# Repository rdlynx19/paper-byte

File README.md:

# Paper Byte

Paper Byte is ESP32-S3 based e-reader,
This repository contains the PCB design files, the CAD files for the case, and the firmware to read and parse EPUB files. 

For a more detailed guide, visit my blog post - [PaperByte](https://pushkardave.com/paper-byte)

## Overview

Paper Byte parses EPUB files straight off an SD card and renders them on an e-ink screen, with three-button navigation (prev / next / select) driving a small state machine: Library, Reader, Menu, Settings, Table of Contents, and a Wi-Fi file transfer mode.

- Unzips and parses EPUBs (XHTML + metadata) from an SD card
- Reflowable text layout: word-wrap, adjustable font size, margins
- Cover art extraction and a library grid with cached thumbnails
- Table of contents / chapter jump
- Persistent reading position per book, survives power loss
- Battery percentage from a MAX17048 fuel gauge
- Sleeps to the book's cover at zero power and wakes straight back into the reader
- Wireless library management: the device hosts its own Wi-Fi access point and a small HTTP page to upload/delete EPUBs

## Hardware

| Component | Role |
|---|---|
| Adafruit ESP32-S3 Feather | Parses EPUBs, drives the display, runs the whole app |
| Waveshare 5" E-Paper Display + driver HAT | Renders pages over SPI |
| Adafruit SD Card module | EPUB storage, hot-swappable (card-detect pin) |
| MAX17048 fuel gauge (on the Feather) | Battery % over I2C |
| 3 tactile switches | Prev / Next / Select |
| 1S LiPo battery | Power, charged over the Feather's USB-C |

A custom through-hole PCB (`pcb/`) ties the Feather, SD module, and e-paper HAT together on SPI buses. The 3D-printed enclosure is in `cad/`.

## Software Architecture

```
EPUB (zip) -> unzip/parse chapter -> word-wrap into pages sized to the display -> render to e-paper
```

- Each chapter is parsed and laid out once, then cached in RAM — flipping pages just re-renders from the cache; only crossing into a new chapter costs a re-parse.
- Reading position, settings, and cover art are all cached to the SD card.

### Code layout (`code/src/`)

- `epub/` — ZIP extraction (`miniz`), XHTML parsing (`tinyxml2` + a small "rubbish" HTML parser), EPUB metadata
- `model/` — page/block layout model that turns parsed HTML into fixed-size pages
- `display/` — e-paper driver (`EPD_5in0`), drawing primitives (`GUI_Paint`), bitmap fonts, cover art rendering
- `storage/` — SD-backed reading position and settings persistence
- `power/` — MAX17048 battery fuel gauge wrapper
- `network/` — `FileServer`, the AP-mode Wi-Fi file manager

## Wireless File Manager

From the Library menu, entering File Transfer mode starts a Wi-Fi access point (SSID/password in `code/src/config.h`) and a small web page for uploading/deleting EPUBs. Idle-timeout sleep is suspended while the mode is active; exiting tears down Wi-Fi and re-scans the library.

## Future Work

- Partial e-ink refresh for page turns (currently a full refresh every page)
- Bookmarks
- A dedicated low-battery/charging screen

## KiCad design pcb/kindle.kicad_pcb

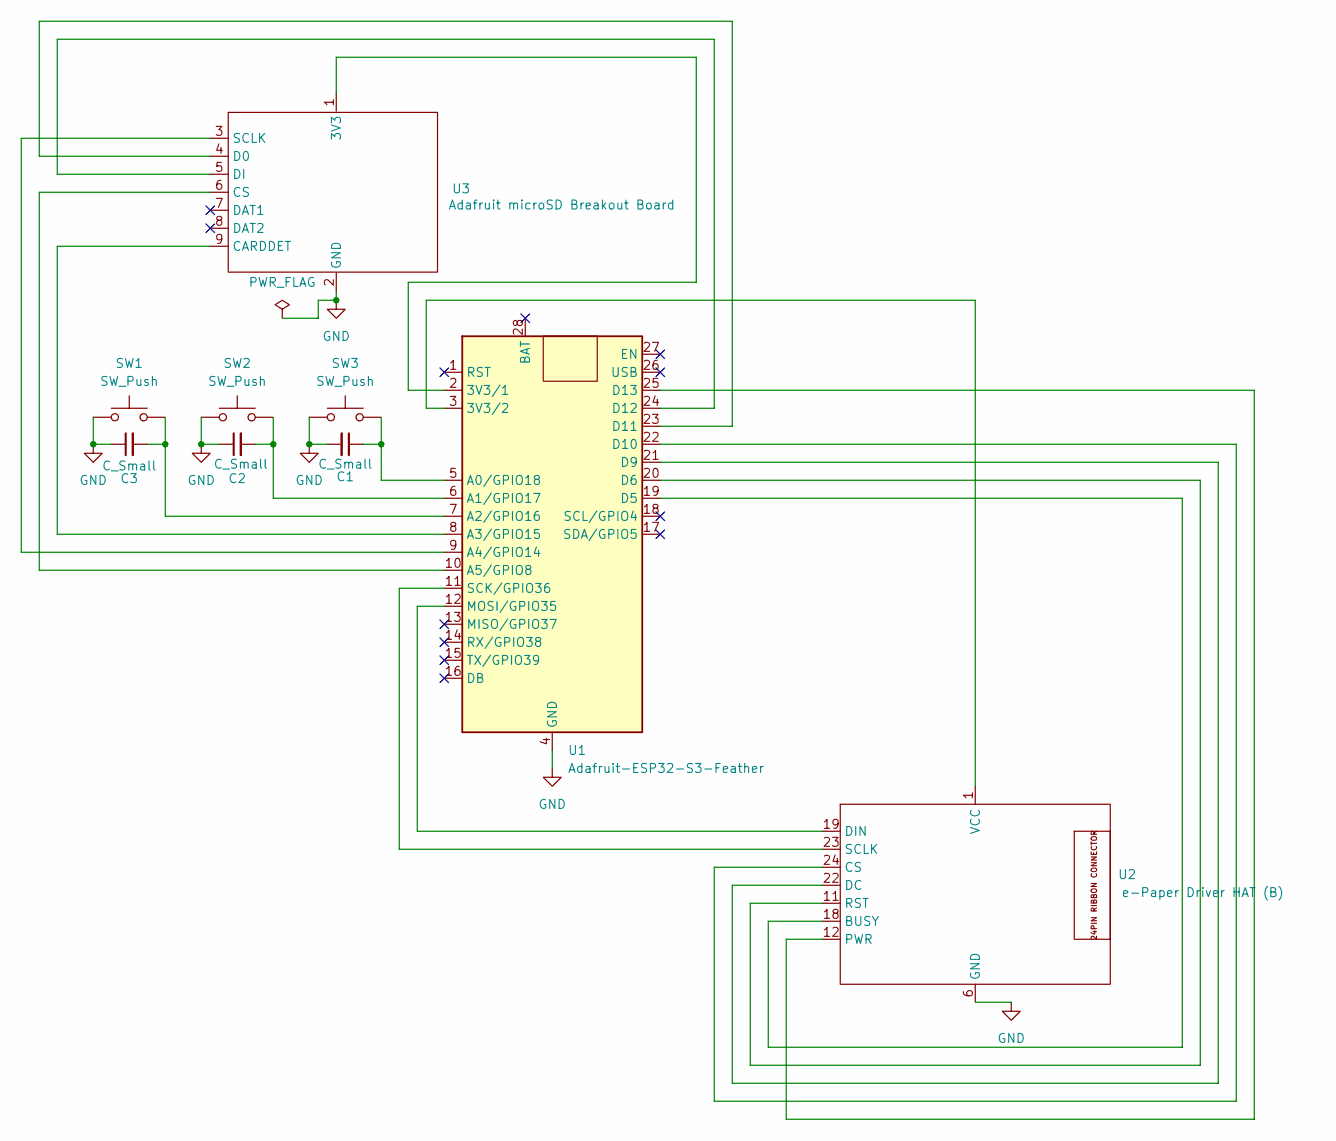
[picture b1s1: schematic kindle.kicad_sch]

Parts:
C1, C2, C3: C_Small; C_Disc_D3.0mm_W1.6mm_P2.50mm
SW1, SW2, SW3: SW_Push; SW_PUSH_6mm_H5mm
U1: Adafruit-ESP32-S3-Feather; Adafruit_ESP32_S3_Feather_WithMountingHoles
U2: e-Paper Driver HAT (B); MODULE_RASPBERRY_PI_ZERO_2_W
U3: Adafruit microSD Breakout Board; MODULE_MICROSD_SPI_OR_SDIO_CARD

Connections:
GND: C1.2, C2.1, C3.1, SW1.1, SW2.1, SW3.1, U1.4 (GND), U2.6 (GND), U3.2 (GND)
unnamed: U1.2 (3V3/1), U3.1 (3V3)
unnamed: U1.3 (3V3/2), U2.1 (VCC)
unnamed: C1.1, SW3.2, U1.5 (A0/GPIO18)
unnamed: C2.2, SW2.2, U1.6 (A1/GPIO17)
unnamed: C3.2, SW1.2, U1.7 (A2/GPIO16)
unnamed: U1.8 (A3/GPIO15), U3.9 (CARDDET)
unnamed: U1.9 (A4/GPIO14), U3.3 (SCLK)
unnamed: U1.10 (A5/GPIO8), U3.6 (CS)
unnamed: U1.19 (D5), U2.18 (BUSY)
unnamed: U1.20 (D6), U2.11 (RST)
unnamed: U1.21 (D9), U2.22 (DC)
unnamed: U1.22 (D10), U2.24 (CS)
unnamed: U1.23 (D11), U3.4 (D0)
unnamed: U1.24 (D12), U3.5 (DI)
unnamed: U1.25 (D13), U2.12 (PWR)
unnamed: U1.12 (MOSI/GPIO35), U2.19 (DIN)
unnamed: U1.11 (SCK/GPIO36), U2.23 (SCLK)

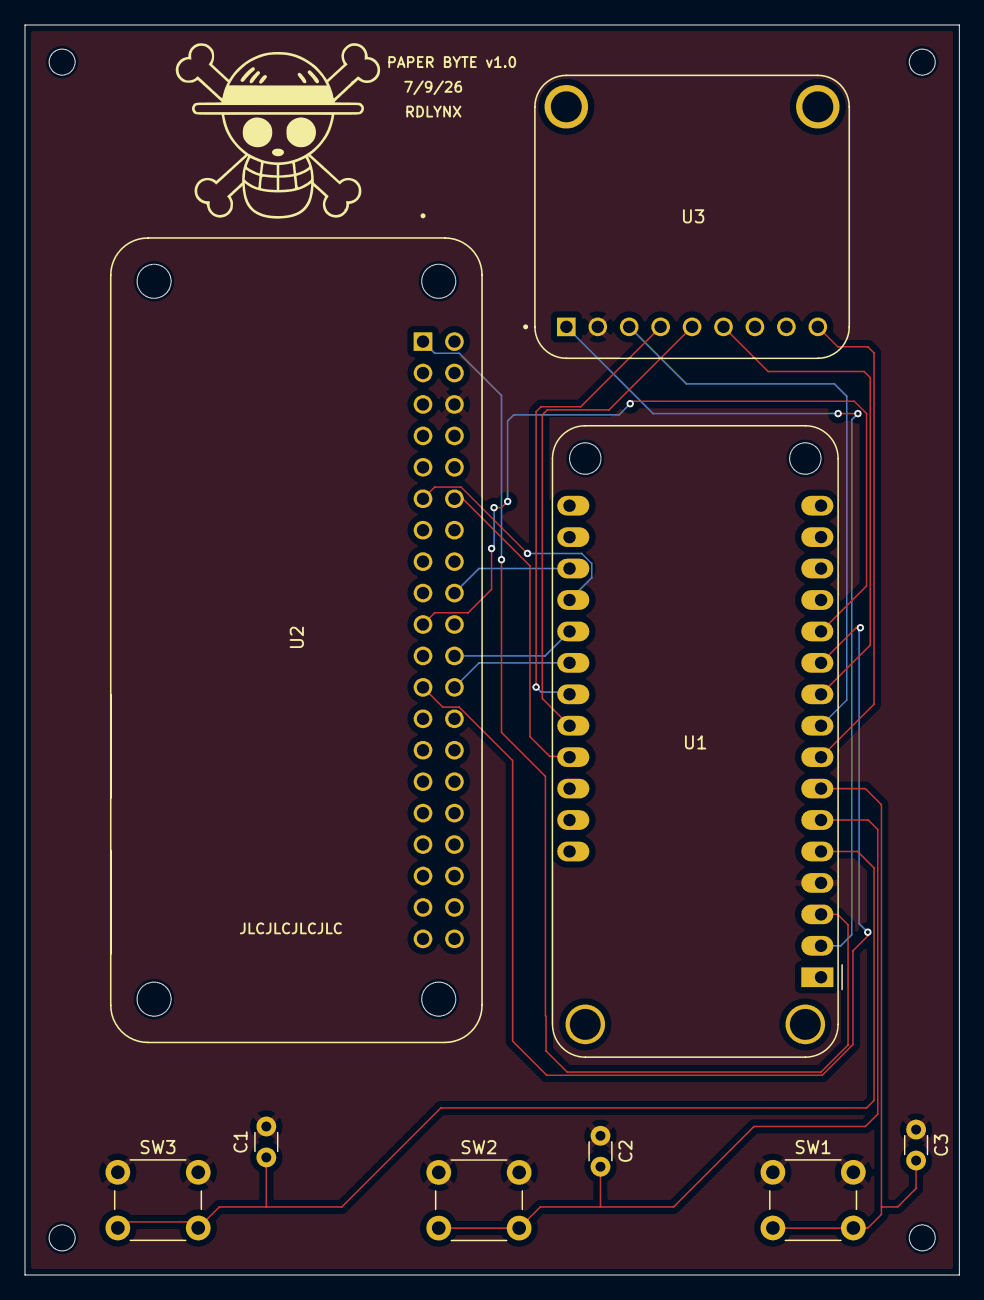
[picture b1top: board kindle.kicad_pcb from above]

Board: 2 copper layers, 75.5 x 101.0 mm, 9 parts (0 on the bottom side), 18 nets.
